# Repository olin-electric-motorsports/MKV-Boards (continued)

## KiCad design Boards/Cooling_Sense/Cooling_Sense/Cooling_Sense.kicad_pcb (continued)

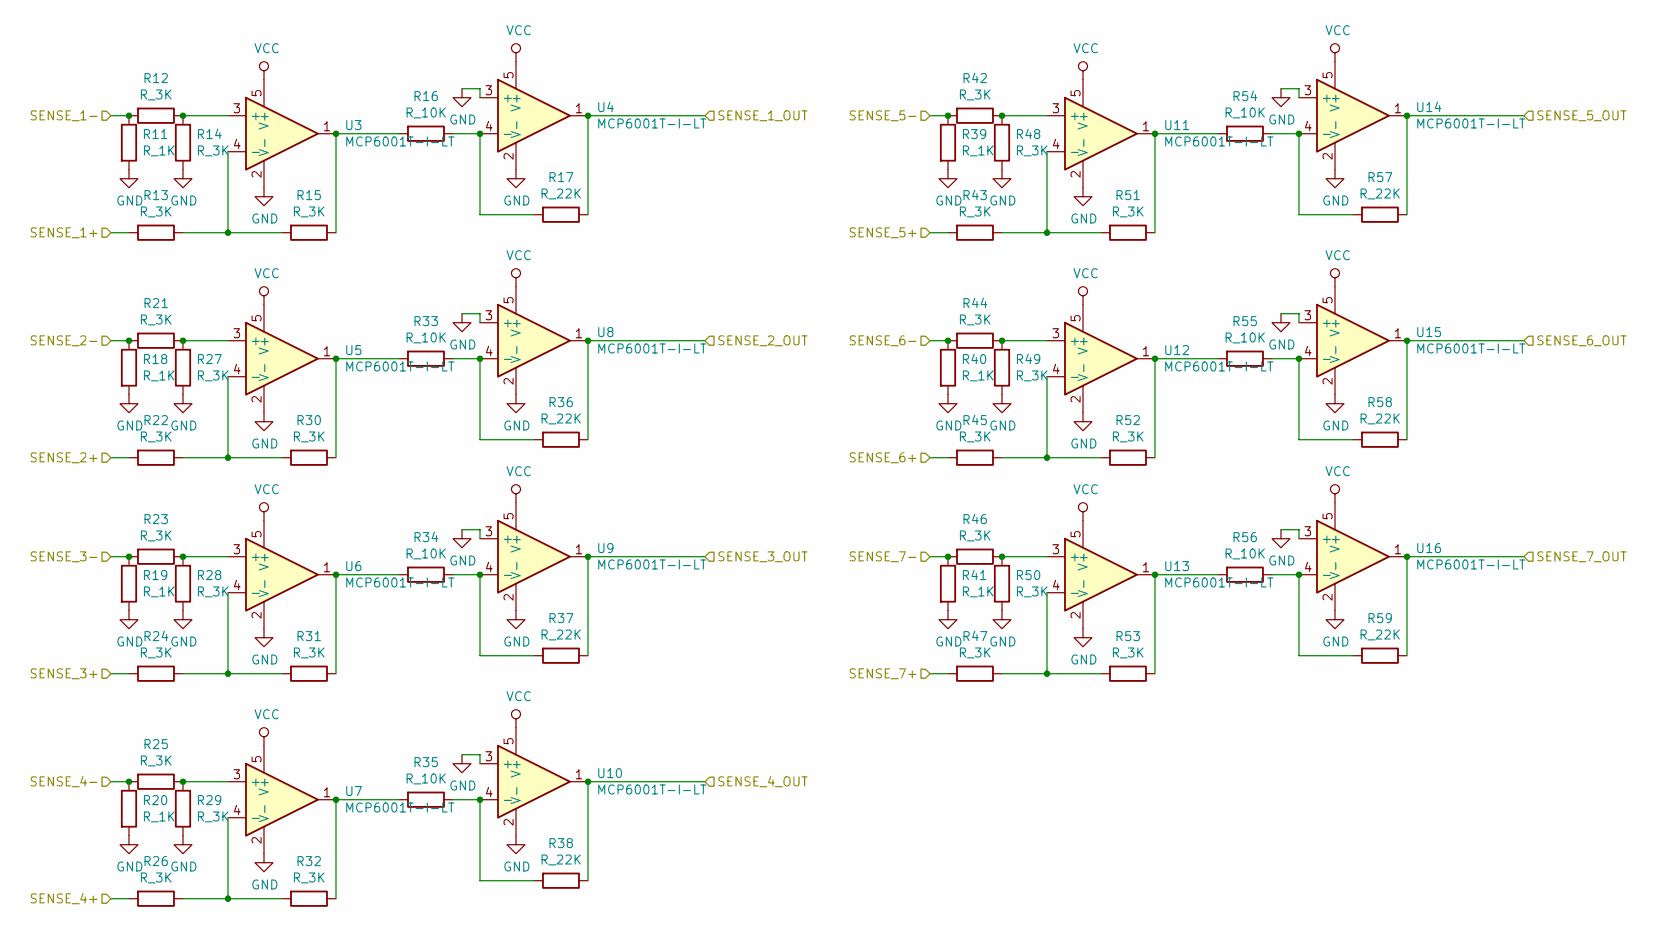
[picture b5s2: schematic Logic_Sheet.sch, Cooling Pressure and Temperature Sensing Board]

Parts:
R11, R18, R19, R20, R39, R40, R41: R_1K; R_0805_OEM; MPN RNCP0805FTD1K00CT-ND
R12, R13, R14, R15, R21, R22, R23, R24, R25, R26, R27, R28, R29, R30, R31, R32, R42, R43, R44, R45, R46, R47, R48, R49, R50, R51, R52, R53: R_3K; R_0805_OEM; MPN RMCF0805FT3K00CT-ND
R16, R33, R34, R35, R54, R55, R56: R_10K; R_0805_OEM; MPN CRS0805-FX-1002ELFCT-ND
R17, R36, R37, R38, R57, R58, R59: R_22K; R_0805_OEM; MPN RMCF0805JT22K0CT-ND
U3, U4, U5, U6, U7, U8, U9, U10, U11, U12, U13, U14, U15, U16: MCP6001T-I-LT; SOT-353_SC-70-5; MPN MCP6001T-I/LTCT-ND

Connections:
/Logic_Sheet/SENSE_1+: R13.2; also elsewhere on the board
/Logic_Sheet/SENSE_1-: R11.1, R12.2; also elsewhere on the board
/Logic_Sheet/SENSE_2+: R22.2; also elsewhere on the board
/Logic_Sheet/SENSE_2-: R18.1, R21.2; also elsewhere on the board
/Logic_Sheet/SENSE_3+: R24.2; also elsewhere on the board
/Logic_Sheet/SENSE_3-: R19.1, R23.2; also elsewhere on the board
/Logic_Sheet/SENSE_4+: R26.2; also elsewhere on the board
/Logic_Sheet/SENSE_4-: R20.1, R25.2; also elsewhere on the board
/Logic_Sheet/SENSE_5+: R43.2; also elsewhere on the board
/Logic_Sheet/SENSE_5-: R39.1, R42.2; also elsewhere on the board
/Logic_Sheet/SENSE_6+: R45.2; also elsewhere on the board
/Logic_Sheet/SENSE_6-: R40.1, R44.2; also elsewhere on the board
/Logic_Sheet/SENSE_7+: R47.2; also elsewhere on the board
/Logic_Sheet/SENSE_7-: R41.1, R46.2; also elsewhere on the board
/READ_1: R17.1, U4.1; also elsewhere on the board
/READ_2: R36.1, U8.1; also elsewhere on the board
/READ_3: R37.1, U9.1; also elsewhere on the board
/READ_4: R38.1, U10.1; also elsewhere on the board
/READ_5: R57.1, U14.1; also elsewhere on the board
/READ_6: R58.1, U15.1; also elsewhere on the board
/READ_7: R59.1, U16.1; also elsewhere on the board
GND: R11.2, R14.1, R18.2, R19.2, R20.2, R27.1, R28.1, R29.1, R39.2, R40.2, R41.2, R48.1, R49.1, R50.1, U3.2 (V-), U4.2 (V-), U4.3 (+), U5.2 (V-), U6.2 (V-), U7.2 (V-), U8.2 (V-), U8.3 (+), U9.2 (V-), U9.3 (+), U10.2 (V-), U10.3 (+), U11.2 (V-), U12.2 (V-), U13.2 (V-), U14.2 (V-), U14.3 (+), U15.2 (V-), U15.3 (+), U16.2 (V-), U16.3 (+); also elsewhere on the board
unnamed: R12.1, R14.2, U3.3 (+)
unnamed: R13.1, R15.2, U3.4 (-)
unnamed: R15.1, R16.2, U3.1
unnamed: R16.1, R17.2, U4.4 (-)
unnamed: R21.1, R27.2, U5.3 (+)
unnamed: R22.1, R30.2, U5.4 (-)
unnamed: R23.1, R28.2, U6.3 (+)
unnamed: R24.1, R31.2, U6.4 (-)
unnamed: R25.1, R29.2, U7.3 (+)
unnamed: R26.1, R32.2, U7.4 (-)
unnamed: R30.1, R33.2, U5.1
unnamed: R31.1, R34.2, U6.1
unnamed: R32.1, R35.2, U7.1
unnamed: R33.1, R36.2, U8.4 (-)
unnamed: R34.1, R37.2, U9.4 (-)
unnamed: R35.1, R38.2, U10.4 (-)
unnamed: R42.1, R48.2, U11.3 (+)
unnamed: R43.1, R51.2, U11.4 (-)
unnamed: R44.1, R49.2, U12.3 (+)
unnamed: R45.1, R52.2, U12.4 (-)
unnamed: R46.1, R50.2, U13.3 (+)
unnamed: R47.1, R53.2, U13.4 (-)
unnamed: R51.1, R54.2, U11.1
unnamed: R52.1, R55.2, U12.1
unnamed: R53.1, R56.2, U13.1
unnamed: R54.1, R57.2, U14.4 (-)
unnamed: R55.1, R58.2, U15.4 (-)
unnamed: R56.1, R59.2, U16.4 (-)
VCC: U3.5 (V+), U4.5 (V+), U5.5 (V+), U6.5 (V+), U7.5 (V+), U8.5 (V+), U9.5 (V+), U10.5 (V+), U11.5 (V+), U12.5 (V+), U13.5 (V+), U14.5 (V+), U15.5 (V+), U16.5 (V+); also elsewhere on the board

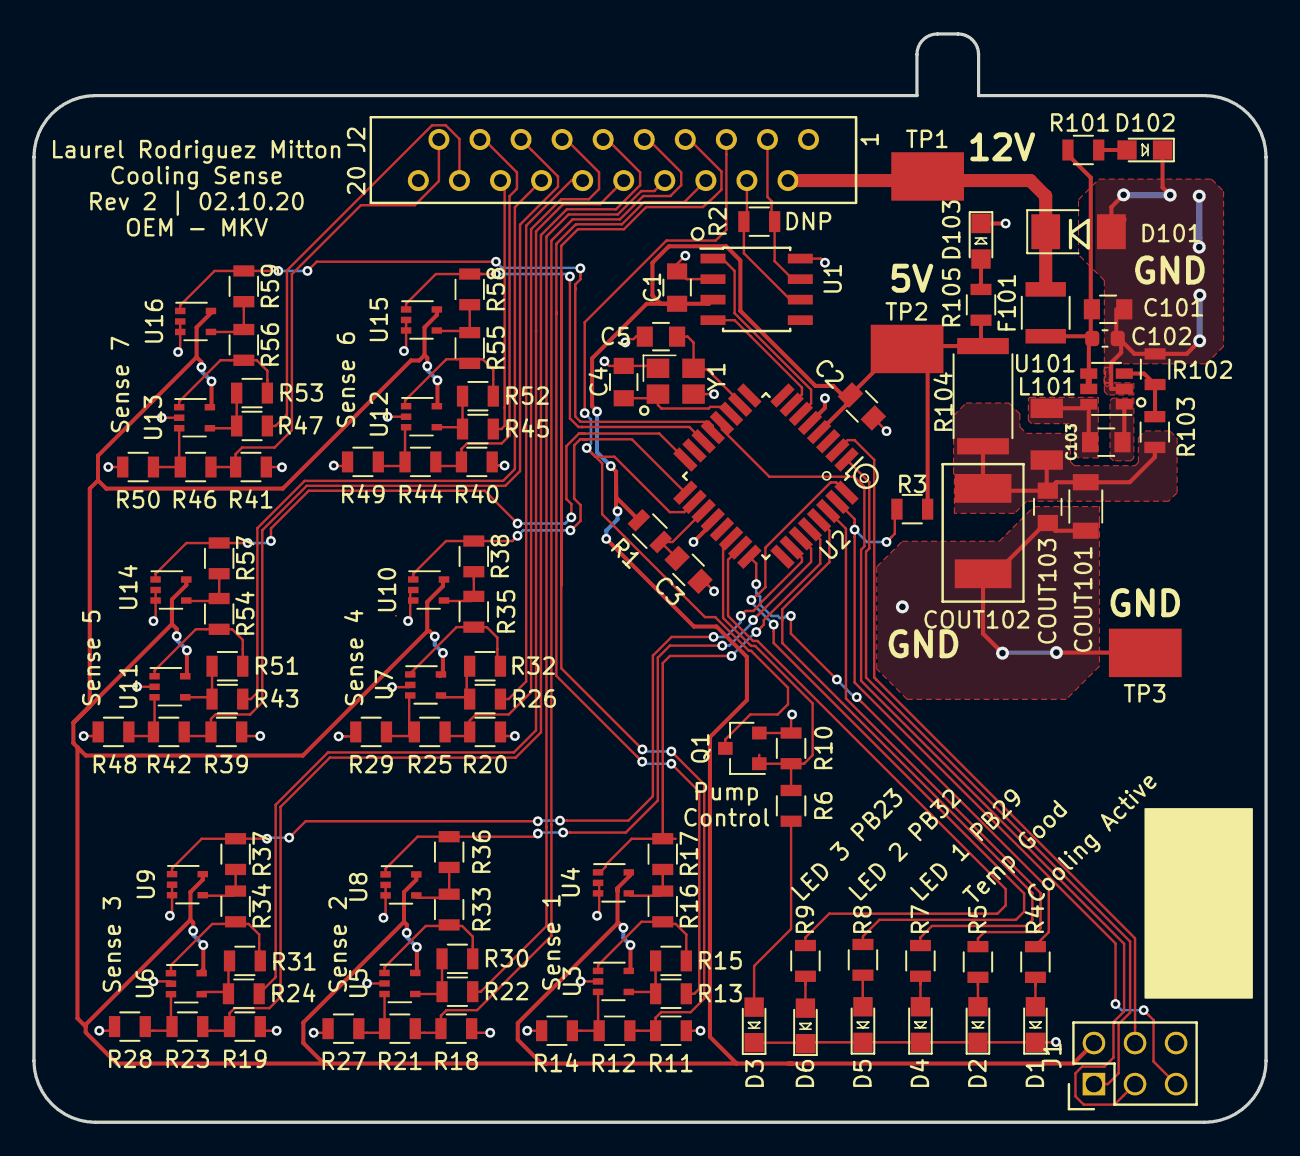
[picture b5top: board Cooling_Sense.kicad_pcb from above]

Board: 2 copper layers, 76.2 x 67.3 mm, 110 parts (0 on the bottom side), 83 nets.

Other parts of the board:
TP1, TP2, TP3: Test_Point_SMD

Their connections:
/12V: TP1.1; also elsewhere on the board
GND: TP3.1; also elsewhere on the board
VCC: TP2.1; also elsewhere on the board

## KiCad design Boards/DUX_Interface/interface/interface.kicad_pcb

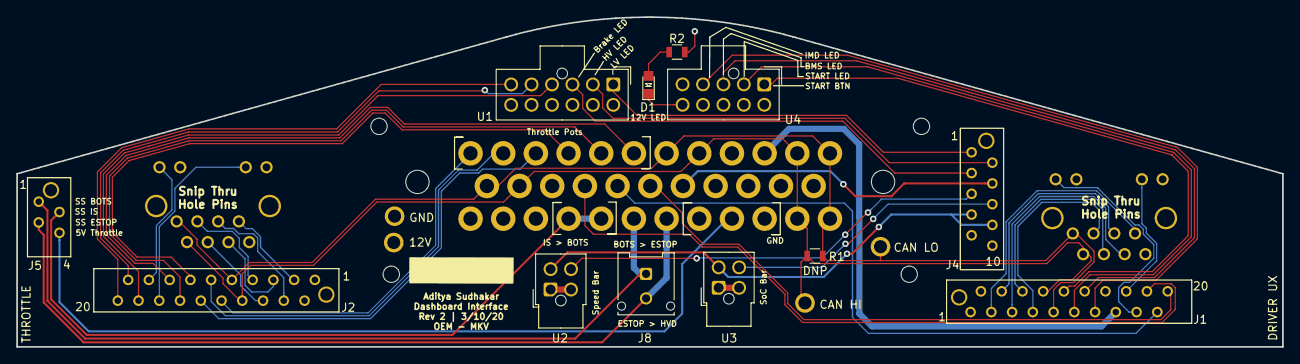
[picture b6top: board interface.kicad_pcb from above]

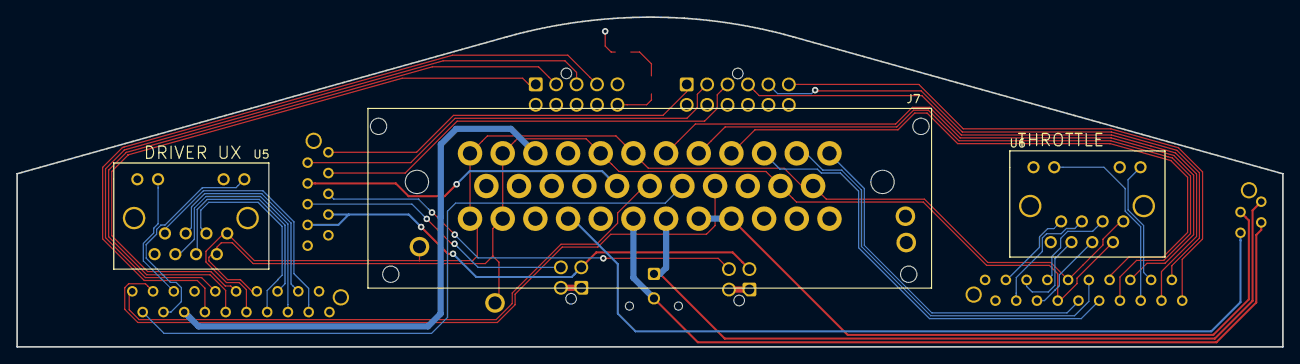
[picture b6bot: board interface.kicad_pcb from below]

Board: 4 copper layers, 154.9 x 40.4 mm, 19 parts (3 on the bottom side), 47 nets.

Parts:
12V: TestPoint; tp_1.6mm
CAN HI: TestPoint; tp_1.6mm
CAN LO: TestPoint; tp_1.6mm
D1: LED_0805; LED_0805_OEM
GND: TestPoint; tp_1.6mm
J1, J2: MM_F_VT_20; micromatch_female_vert_20
J4: MM_F_VT_10; micromatch_female_vert_10
J5: MM_F_VT_04; micromatch_female_vert_4
J7: Ampseal_35_VT; Ampseal_35
J8: MicroFit_RA_V_2; Molex_Micro-Fit_3.0_43045-0212_2x01_P3.00mm_Vertical
R1: R_120_DNP; R_0805_OEM
R2: R_1K; R_0805_OEM
U1: Nanofit_12; Molex_Nano-Fit_105310-xx12_2x06_P2.50mm_Vertical
U2, U3: Nanofit_4; Molex_Nano-Fit_105310-xx04_2x02_P2.50mm_Vertical
U4: Nanofit_10; Molex_Nano-Fit_105310-xx10_2x05_P2.50mm_Vertical
U5, U6: RJ45_VT; RJ45-Vertical

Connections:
+12V: 12V.1, J1.2, J2.2, J7.2, J7.3, J7.21, J7.22, R2.2
/5V_CAN_LOGGER: J5.4, J7.9
/5V_DUX: J1.3, U5.7
/5V_LED_BARS: J4.7, J4.8, U2.3, U3.3
/5V_STEERING: J4.4, J7.19
/5V_THROTTLE: J2.3, U6.7
/BMS_LED: J1.12, U4.3
/BOTS>ESTOP: J5.1, J7.6, J8.1
/BRAKE_LED: J4.3, U1.3
/CAN+: CAN HI.1, J1.8, J2.8, J7.11, J7.14, J7.31, J7.34, R1.2, U5.2, U6.2
/CAN-: CAN LO.1, J1.9, J2.9, J7.12, J7.13, J7.30, J7.35, R1.1, U5.1, U6.1
/DRIVE_MODE_+: J2.18, U1.4
/DRIVE_MODE_-: J2.20, U1.6
/DRIVE_MODE_SENSE: J2.19, U1.5
/ESTOP>HVD: J5.3, J7.7, J8.2
/HV_LED: J4.2, U1.2
/IMD_LED: J1.13, U4.4
/IS>BOTS: J5.2, J7.4, J7.5
/LV_LED: J4.1, U1.1
/MISO_DUX: J1.4, U5.5
/MISO_THROTTLE: J2.4, U6.5
/MOSI_DUX: J1.5, U5.6
/MOSI_THROTTLE: J2.5, U6.6
/RESET_DUX: J1.7, U5.3
/RESET_THROTTLE: J2.7, U6.3
/RJ45_LED_G_DUX: J1.17, U5.12
/RJ45_LED_G_THROTTLE: J2.17, U6.12
/RJ45_LED_O_DUX: J1.16, U5.10
/RJ45_LED_O_THROTTLE: J2.16, U6.10
/RTD_LSD: J1.15, J7.33
/SCK_DUX: J1.6, U5.4
/SCK_THROTTLE: J2.6, U6.4
/SOC_LED_BAR: J4.6, U3.4
/SPEED_LED_BAR: J4.5, U2.4
/START_BTN: J1.10, U4.1
/START_LED: J1.11, U4.2
/STEERING_POT_+: J1.18, J7.16
/STEERING_POT_-: J1.20, J7.18
/STEERING_POT_SENSE: J1.19, J7.17
/THROTTLE_POT_1_+: J2.10, J7.24
/THROTTLE_POT_1_-: J2.12, J7.26
/THROTTLE_POT_1_SENSE: J2.11, J7.25
/THROTTLE_POT_2_+: J2.13, J7.27
/THROTTLE_POT_2_-: J2.15, J7.29
/THROTTLE_POT_2_SENSE: J2.14, J7.28
GND: D1.1, GND.1, J1.1, J1.14, J2.1, J4.9, J4.10, J7.1, J7.8, J7.10, J7.15, J7.20, J7.23, J7.32, U1.7, U1.8, U1.9, U1.10, U1.11, U1.12, U2.1, U2.2, U3.1, U3.2, U4.5, U4.6, U4.7, U4.8, U4.9, U4.10, U5.8, U5.9, U5.11, U5.13, U5.14, U6.8, U6.9, U6.11, U6.13, U6.14
unnamed: D1.2, R2.1

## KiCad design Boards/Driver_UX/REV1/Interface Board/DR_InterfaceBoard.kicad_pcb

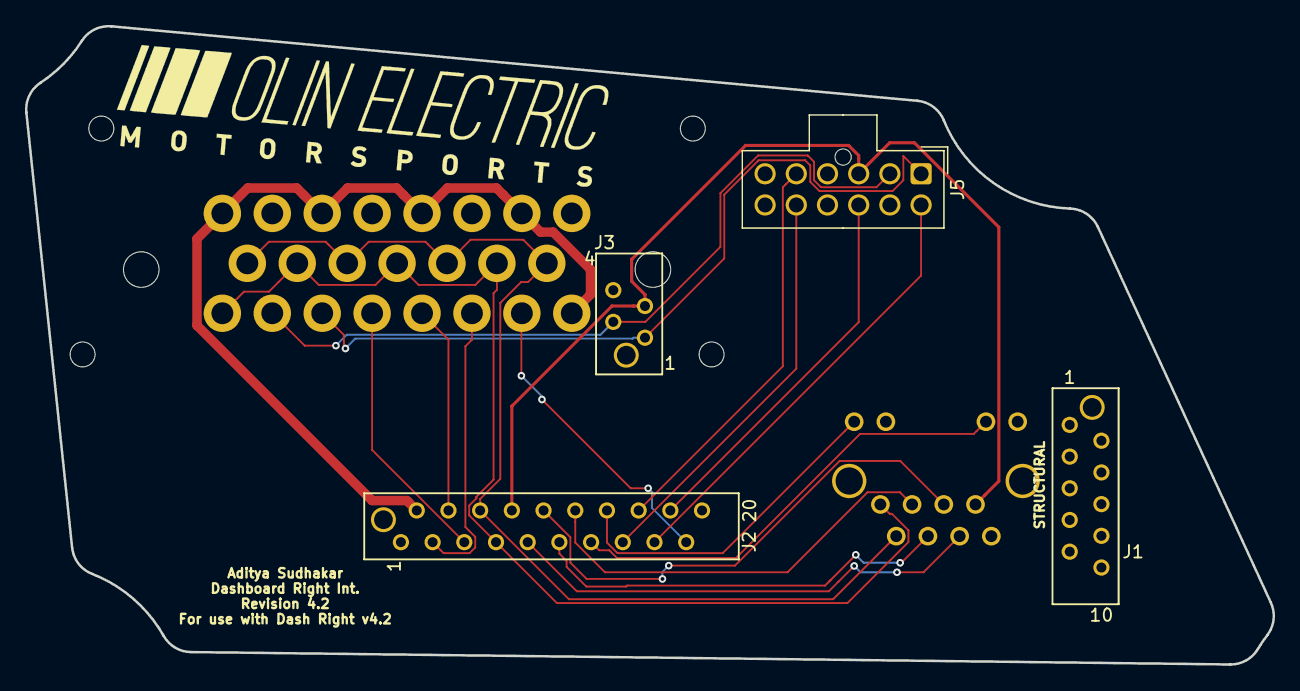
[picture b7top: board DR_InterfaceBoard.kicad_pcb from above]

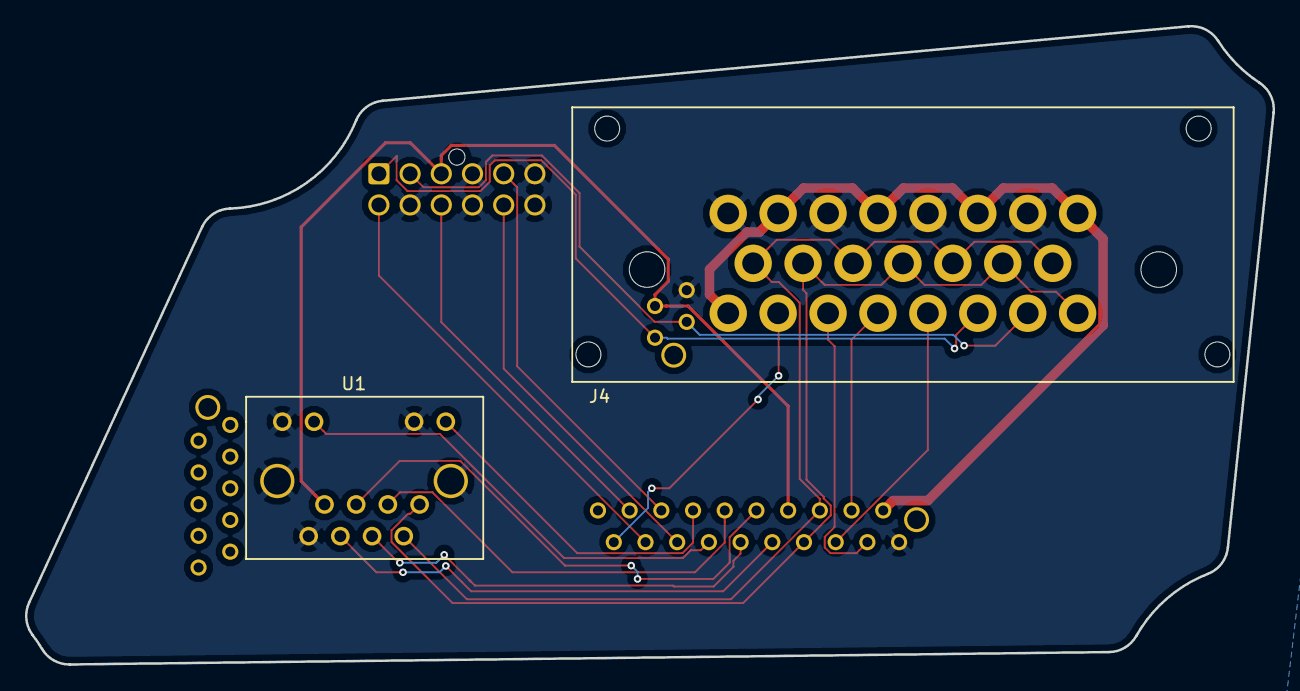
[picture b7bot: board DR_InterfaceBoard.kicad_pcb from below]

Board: 2 copper layers, 100.0 x 51.1 mm, 6 parts (2 on the bottom side), 21 nets.

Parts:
J1: MM_F_VT_10; micromatch_female_vert_10
J2: MM_F_VT_20; micromatch_female_vert_20
J3: MM_F_VT_04; micromatch_female_vert_4
J4: Ampseal_23_VT; Ampseal_23
J5: NanoFit_12; Molex_Nano-Fit_105310-xx12_2x06_P2.50mm_Vertical
U1: RJ45_VT; RJ45-Vertical

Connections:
+5V: J2.8, J3.3, J5.3, U1.7
+12V: J2.2, J4.2, J4.4, J4.6, J4.8, J4.16
/BMS_LED: J2.16, J5.5
/CANH: J2.6, J4.9, J4.11, J4.13, J4.15, U1.2
/CANL: J2.7, J4.10, J4.12, J4.14, J4.23, U1.1
/IMD_LED: J2.17, J5.7
/MISO: J2.10, U1.5
/MOSI: J2.9, U1.6
/RESET: J2.12, U1.3
/RJ45_LED1: J2.13, U1.10
/RJ45_LED2: J2.14, U1.12
/RTD_LSD: J2.19, J4.17
/SCK: J2.11, U1.4
/SCL: J3.1, J4.21, J5.1
/SDA: J3.2, J4.22, J5.2
/START_BTN: J2.18, J5.9
/START_LED: J2.15, J5.11
/STR_POT+: J2.3, J4.18
/STR_POT-: J2.5, J4.20
/STR_POT_SENSE: J2.4, J4.19
GND: J2.1, J3.4, J4.1, J4.3, J4.5, J4.7, J5.4, J5.6, J5.8, J5.10, J5.12, U1.8, U1.9, U1.11, U1.13, U1.14
